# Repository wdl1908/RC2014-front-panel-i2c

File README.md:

# Front Panel I2C Adapter, Designed For RC2014

An I2C adapter board for the RC2014 Blue Box front panel.

The RC2014 [Universal Front Panel I/O Kit](https://z80kits.com/shop/universal-front-panel-switch-and-led-for-romwbw/)
is one kit, but ships as two separate PCBs connected by a ribbon cable: the
**I/O Module** (plugs into the RC2014 backplane, decodes I/O port 0, drives
the LED/switch logic over the Z80 I/O bus, includes a DS1233 reset
supervisor) and the **Front Panel** (the physical board carrying the actual
8 switches and 8 LEDs plus reset switch/power LED, no logic of its own).

This adapter replaces the I/O Module only. The Front Panel board is
unchanged. This adapter's J1 is a female socket that mates directly onto
the Front Panel board's own male header, board-to-board, no cable involved.
It drives the same 8 switches/8 LEDs over I2C through a single TCA9555
16-bit I/O expander (one register bank for switch input, one for LED
output) instead of the Z80 I/O bus board.

Real board photos (phone camera, lighting still a work in progress):

> Note: z80kits also sells a larger "Blue Box Front Panel Kit for RomWBW"
> bundle, with the same two boards plus an LCD module and enclosure-specific
> parts for the Blue Box case. This adapter replaces the same I/O Module
> board in either kit.

## Status

Hardware-confirmed working, both directions (LEDs out, switches in),
including graceful degradation when the board is unplugged (system boots
fine without it, front panel simply reports not present). See `kicad/` for
the full schematic/PCB source, `fab/` for ready-to-order fabrication files,
and `images/` for reference renders.

## Ordering / building

`fab/` contains everything needed to order this board pre-assembled from
JLCPCB:

- `front_panel_i2c_adapter_gerbers.zip`, board gerbers/drill files
- `front_panel_i2c_adapter_bom_jlcpcb.csv`, BOM in JLCPCB's SMT
  assembly upload format
- `front_panel_i2c_adapter_cpl.csv`, component placement (CPL) file,
  same upload flow

Upload the gerbers zip under PCB, then the BOM + CPL pair under SMT
Assembly. Editable KiCad source (schematic + PCB + project + local
symbol/footprint libraries) is in `kicad/`.

## Connectors

- **J1 (Front Panel connector), watch the orientation.** J1 mates directly
  onto the Front Panel board's own male header, and pin 1 has to line up in
  the correct direction. There is no dedicated pin 1 marker on the
  silkscreen (an oversight, not fixed on this revision), but the "J1"
  reference text itself is silkscreened right next to pin 1, so that's
  your cue once it's soldered on. Check pin 1 against the schematic/KiCad
  source before mating the boards if in doubt.
- **J2 (`I2C_IN`), upstream I2C.** 4-pin header, the board's only external
  link to the bus: pin 1 VCC, pin 2 GND, pin 3 SDA, pin 4 SCL.
- **J3 (`RESET_TP`), reset breakout, needs a wire.** The board carries a
  DS1233-5 reset supervisor, wired-OR onto the same Reset net as the Front
  Panel board's manual reset switch (via J1 pin 19). That combined Reset
  net is broken out to J3, a 2-pin header (RESET, GND). J3 is not wired to
  anything else on the board. Run a wire from J3 to wherever the reset
  switch's net is accessible on your backplane, RC2014 backplanes don't
  expose `~RESET` at the card-edge slots directly.
- **JP1/JP2/JP3, TCA9555 address select.** Solder-bridge jumpers for the
  TCA9555's A0/A1/A2 address pins, open (unbridged) by default, giving the
  board's default I2C address of `0x20`. Bridge the corresponding jumper(s)
  to change the address, e.g. if you need more than one of this board on
  the same bus.

## RomWBW driver

Front panel support over I2C requires a matching change to RomWBW's HBIOS
front panel driver (`FP_DETECT`/`FP_SETLEDS`/`FP_GETSWITCHES`). That driver
is written and hardware-confirmed against this board, but not yet published
upstream, still going through a final review pass.

**Driver link: pending, will be added here once published.**

### Build config

Once the driver is available, these are the config values used to build
RomWBW against this board (RC2014 Zed/Zed Pro target). This board is a
plain I2C slave, it needs a working I2C bus master already on the system,
either a real PCF8584 chip or the bitbang driver, not both:

| Setting | Value | Meaning |
|---|---|---|
| `I2CPCFENABLE` | `TRUE` | Enable the PCF8584 I2C bus master (real chip). Mutually exclusive with `I2CBITENABLE` |
| `I2CBITENABLE` | `FALSE` | Enable the bitbang I2C bus master (SC137) instead of a real PCF8584 chip. Mutually exclusive with `I2CPCFENABLE`, set this `TRUE` and `I2CPCFENABLE` `FALSE` if you don't have a PCF8584 |
| `FPLED_ENABLE` | `TRUE` | Enable front panel LEDs |
| `FPSW_ENABLE` | `TRUE` | Enable front panel switches |
| `FP_USE_I2C` | `TRUE` | Drive the front panel over I2C instead of the Z80 I/O bus |
| `FP_I2CADR` | `$20` | TCA9555 7-bit I2C address, with A0/A1/A2 tied low (board default, adjust if you've jumpered a different address) |
| `FPLED_INV` | `FALSE` (default) | TCA9555 output is active-high, no inversion needed |

LEDs and switches share the one TCA9555 chip/address. Register select
(Port 0 = switches/input, Port 1 = LEDs/output) is handled by the driver,
not a config option.

## License

[CERN-OHL-W v2](LICENSE) (CERN Open Hardware Licence, Weakly Reciprocal
variant).

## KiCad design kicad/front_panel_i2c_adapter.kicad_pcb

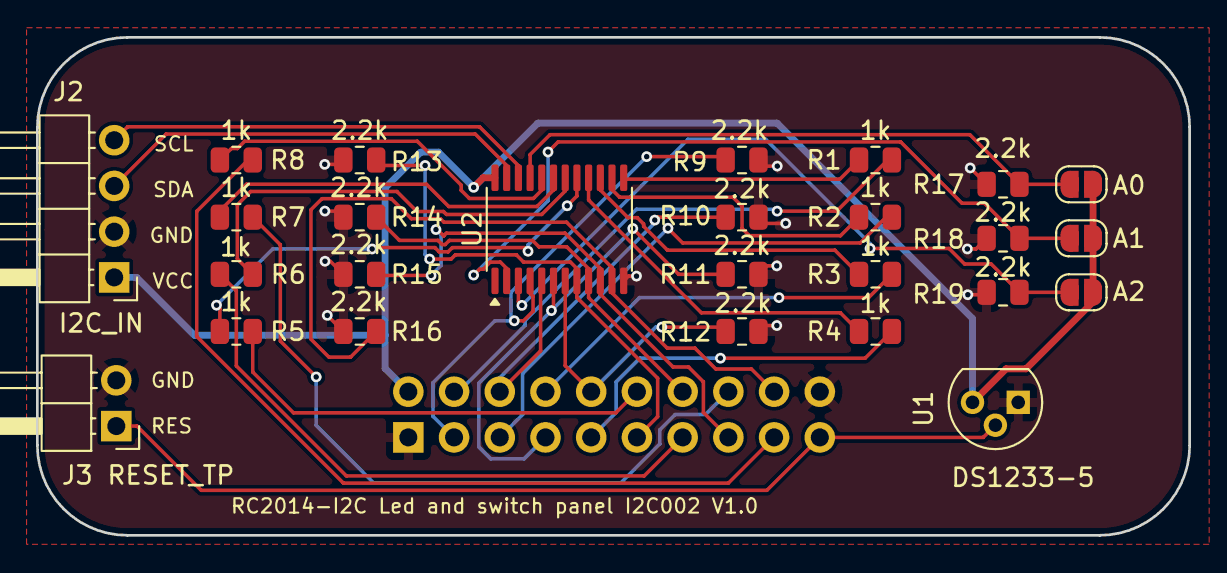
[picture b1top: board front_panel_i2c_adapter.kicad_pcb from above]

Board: 2 copper layers, 64.0 x 27.7 mm, 27 parts (1 on the bottom side), 32 nets.

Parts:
A0, A1, A2: SolderJumper_2_Open; SolderJumper-2_P1.3mm_Open_RoundedPad1.0x1.5mm
J1: TO_PANEL; PinSocket_2x10_P2.54mm_Vertical
J2: I2C_IN; PinHeader_1x04_P2.54mm_Horizontal
J3: RESET_TP; PinHeader_1x02_P2.54mm_Horizontal
R1, R2, R3, R4, R5, R6, R7, R8: 1k; R_0805_2012Metric
R9, R10, R11, R12, R13, R14, R15, R16, R17, R18, R19: 2.2k; R_0805_2012Metric
U1: DS1233-5; TO-92
U2: TCA9555PWR; TSSOP-24_4.4x7.8mm_P0.65mm

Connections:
/GND: J1.1, J1.20, J2.2, J3.2, R9.1, R10.1, R11.1, R12.1, R13.1, R14.1, R15.1, R16.1, R17.1, R18.1, R19.1, U1.1, U2.12 (GND)
/LED0: J1.4, R1.1
/LED1: J1.5, R2.1
/LED2: J1.8, R3.1
/LED3: J1.9, R4.1
/LED4: J1.12, R5.1
/LED5: J1.13, R6.1
/LED6: J1.16, R7.1
/LED7: J1.17, R8.1
/RESET: J1.19, J3.1, U1.2
/SCL: J2.4, U2.22 (SCL)
/SDA: J2.3, U2.23 (SDA)
/SW0: J1.3, R9.2, U2.4 (P00)
/SW1: J1.6, R10.2, U2.5 (P01)
/SW2: J1.7, R11.2, U2.6 (P02)
/SW3: J1.10, R12.2, U2.7 (P03)
/SW4: J1.11, R13.2, U2.8 (P04)
/SW5: J1.14, R14.2, U2.9 (P05)
/SW6: J1.15, R15.2, U2.10 (P06)
/SW7: J1.18, R16.2, U2.11 (P07)
/VCC: A0.2 (B), A1.2 (B), A2.2 (B), J1.2, J2.1, U1.3, U2.24 (VCC)
unnamed: A0.1 (A), R17.2, U2.21 (A0)
unnamed: A1.1 (A), R18.2, U2.2 (A1)
unnamed: A2.1 (A), R19.2, U2.3 (A2)
unnamed: R1.2, U2.13 (P10)
unnamed: R2.2, U2.14 (P11)
unnamed: R3.2, U2.15 (P12)
unnamed: R4.2, U2.16 (P13)
unnamed: R5.2, U2.17 (P14)
unnamed: R6.2, U2.18 (P15)
unnamed: R7.2, U2.19 (P16)
unnamed: R8.2, U2.20 (P17)

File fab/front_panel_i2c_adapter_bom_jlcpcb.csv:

Comment,Designator,Footprint,LCSC Part #
1k,"R1,R2,R3,R4,R5,R6,R7,R8",Resistor_SMD:R_0805_2012Metric,
2.2k,"R9,R10,R11,R12,R13,R14,R15,R16,R17,R18,R19",Resistor_SMD:R_0805_2012Metric,
TCA9555PWR,U2,Package_SO:TSSOP-24_4.4x7.8mm_P0.65mm,
